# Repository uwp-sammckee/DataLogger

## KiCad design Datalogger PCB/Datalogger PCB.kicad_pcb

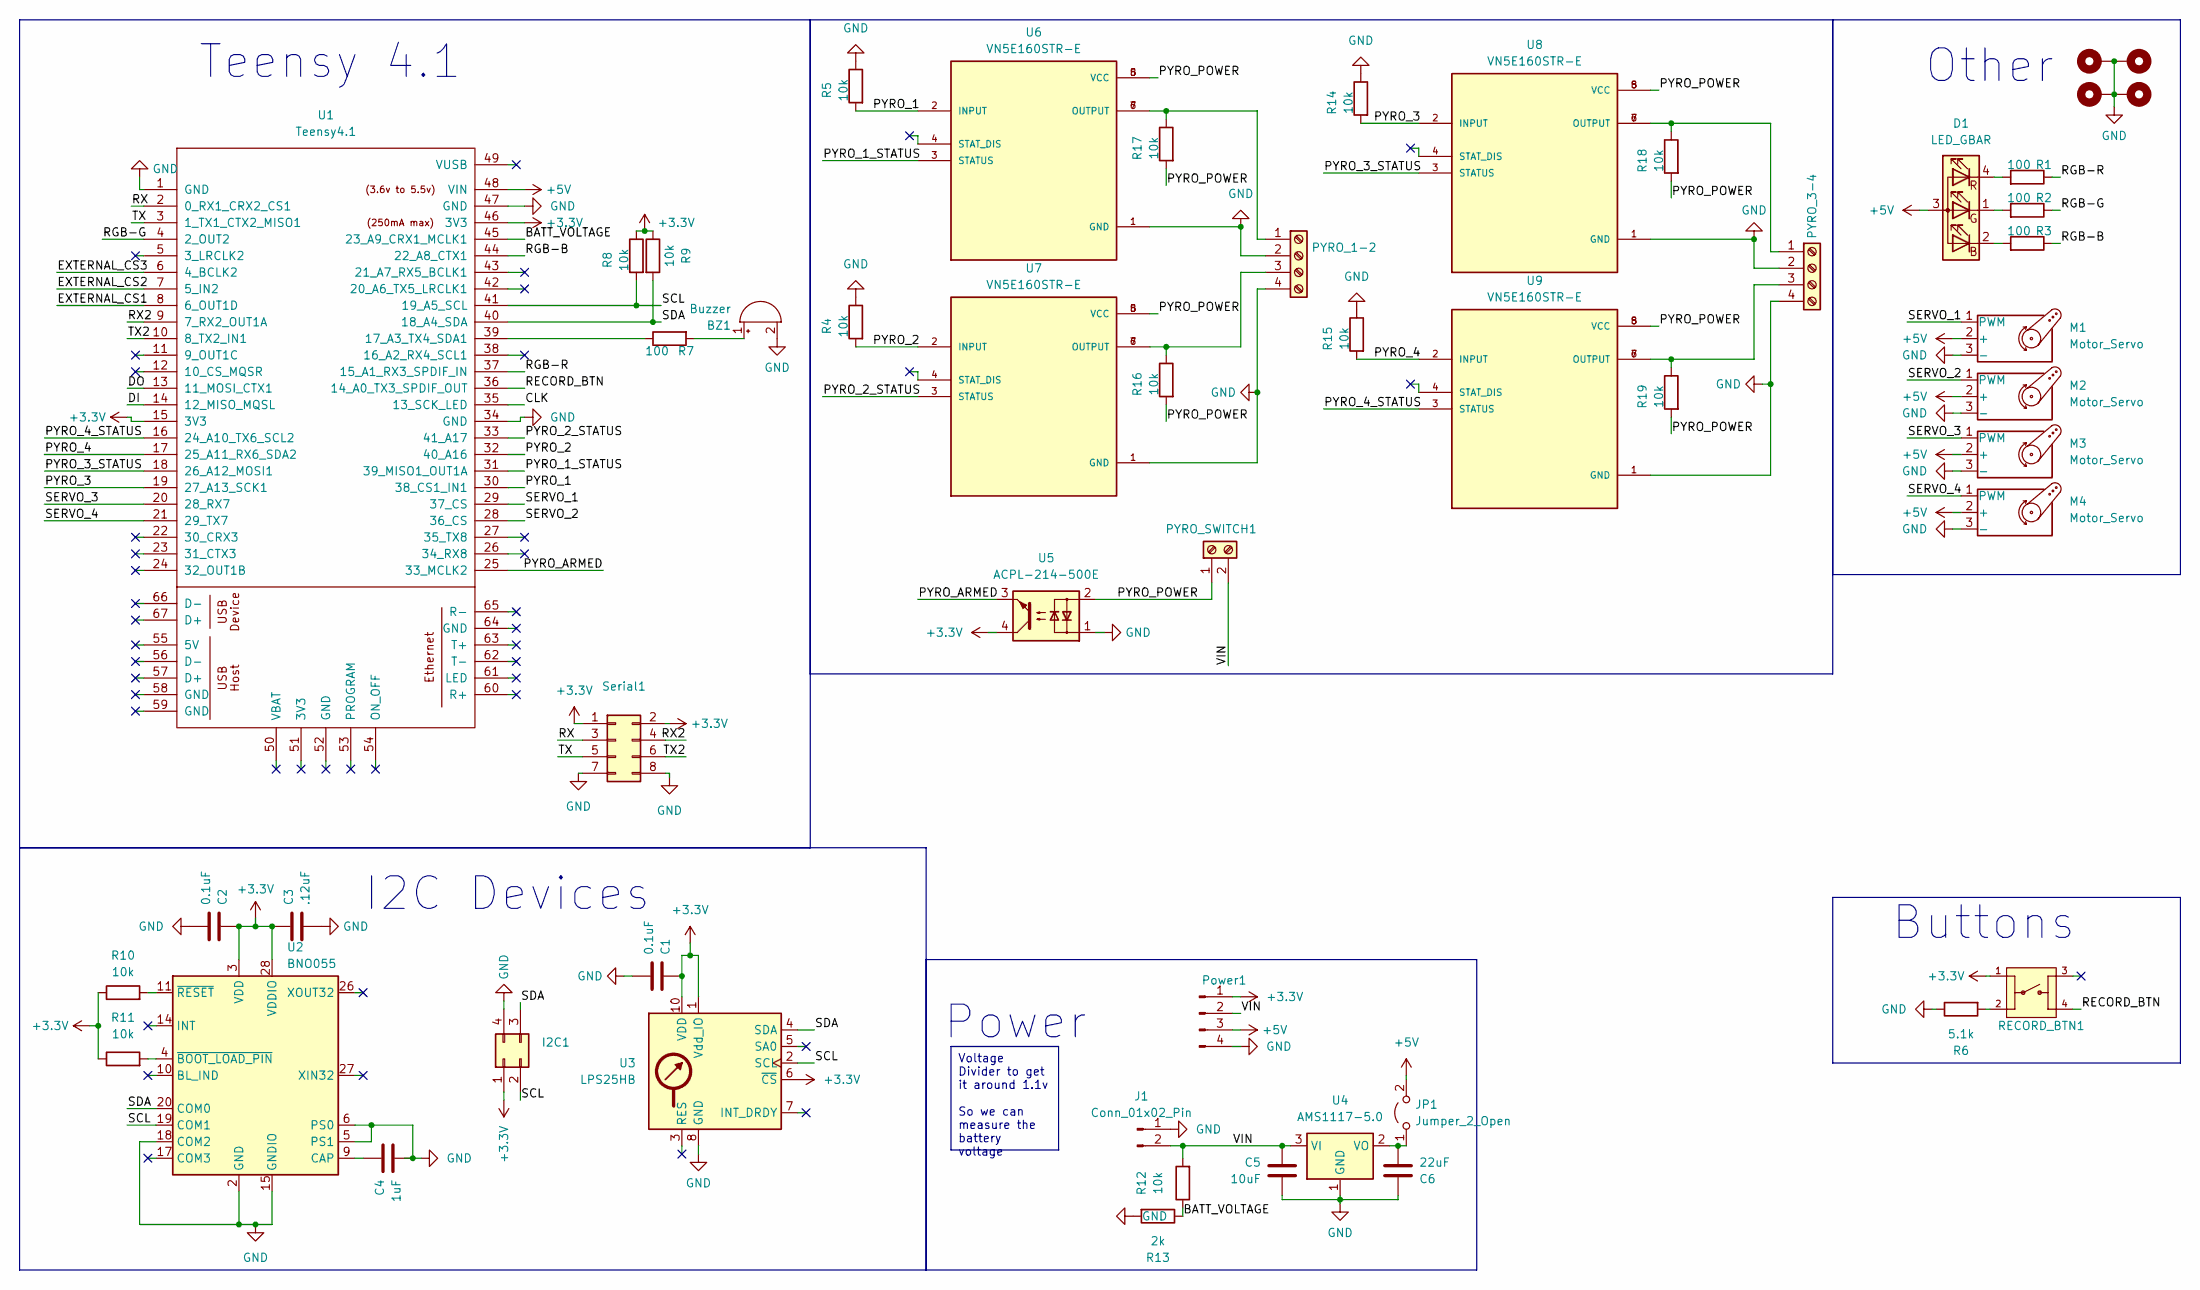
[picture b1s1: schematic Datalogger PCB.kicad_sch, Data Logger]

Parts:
BZ1: Buzzer; Buzzer_12x9.5RM7.6
C1, C2: 0.1uF; R_0603_1608Metric_Pad0.98x0.95mm_HandSolder
C3: .12uF; R_0603_1608Metric_Pad0.98x0.95mm_HandSolder
C4: 1uF; R_0603_1608Metric_Pad0.98x0.95mm_HandSolder
C5: 10uF; R_0603_1608Metric_Pad0.98x0.95mm_HandSolder
C6: 22uF; R_0603_1608Metric_Pad0.98x0.95mm_HandSolder
D1: LED_GBAR
H1, H2, H3, H4: MountingHole_Pad; MountingHole_3.2mm_M3_Pad_TopBottom
I2C1: Conn_02x02_Counter_Clockwise; PinHeader_2x02_P2.54mm_Vertical
J1: Conn_01x02_Pin; PinHeader_1x02_P2.54mm_Vertical
JP1: Jumper_2_Open; PinHeader_1x02_P2.54mm_Vertical
M1, M2, M3, M4: Motor_Servo; PinHeader_1x03_P2.54mm_Vertical
PYRO_1-2, PYRO_3-4: Screw_Terminal_01x04; TerminalBlock_bornier-4_P5.08mm
PYRO_SWITCH1: Screw_Terminal_01x02; TerminalBlock_bornier-2_P5.08mm
Power1: Conn_01x04_Pin; PinHeader_1x04_P2.54mm_Vertical
R1, R2, R3, R7: 100; R_0603_1608Metric_Pad0.98x0.95mm_HandSolder
R4, R5, R8, R9, R10, R11, R12, R14, R15, R16, R17, R18, R19: 10k; R_0603_1608Metric_Pad0.98x0.95mm_HandSolder
R6: 5.1k; R_0603_1608Metric_Pad0.98x0.95mm_HandSolder
R13: 2k; R_0603_1608Metric_Pad0.98x0.95mm_HandSolder
RECORD_BTN1: FSM8JH; SW_FSM8JH; PARTREV C10
Serial1: Conn_02x04_Odd_Even; PinHeader_2x04_P2.54mm_Vertical
U1: Teensy4.1; Teensy41
U2: BNO055; LGA-28_5.2x3.8mm_P0.5mm
U3: LPS25HB; ST_HLGA-10_2.5x2.5mm_P0.6mm_LayoutBorder3x2y
U4: AMS1117-5.0; SOT-223-3_TabPin2
U5: ACPL-214-500E; SOP-4_4.4x2.6mm_P1.27mm
U6, U7, U8, U9: VN5E160STR-E; SOIC127P600X175-8N; PARTREV 3

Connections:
+3.3V: C1.1, C2.1, C3.1, I2C1.1, Power1.1, R8.1, R9.1, R10.1, R11.1, RECORD_BTN1.1, Serial1.1, Serial1.2, U1.15 (3V3), U1.46 (3V3), U2.3 (VDD), U2.28 (VDDIO), U3.1 (Vdd_IO), U3.6 (~CS), U3.10 (VDD), U5.4
+5V: D1.3 (A), JP1.2 (B), M1.2 (+), M2.2 (+), M3.2 (+), M4.2 (+), Power1.3, U1.48 (VIN)
/BATT_VOLTAGE: R12.1, R13.1, U1.45 (23_A9_CRX1_MCLK1)
/CLK: U1.35 (13_SCK_LED)
/DI: U1.14 (12_MISO_MQSL)
/DO: U1.13 (11_MOSI_CTX1)
/EXTERNAL_CS1: U1.8 (6_OUT1D)
/EXTERNAL_CS2: U1.7 (5_IN2)
/EXTERNAL_CS3: U1.6 (4_BCLK2)
/PYRO_1: R5.2, U1.30 (38_CS1_IN1), U6.2 (INPUT)
/PYRO_1_STATUS: U1.31 (39_MISO1_OUT1A), U6.3 (STATUS)
/PYRO_2: R4.2, U1.32 (40_A16), U7.2 (INPUT)
/PYRO_2_STATUS: U1.33 (41_A17), U7.3 (STATUS)
/PYRO_3: R14.2, U1.19 (27_A13_SCK1), U8.2 (INPUT)
/PYRO_3_STATUS: U1.18 (26_A12_MOSI1), U8.3 (STATUS)
/PYRO_4: R15.2, U1.17 (25_A11_RX6_SDA2), U9.2 (INPUT)
/PYRO_4_STATUS: U1.16 (24_A10_TX6_SCL2), U9.3 (STATUS)
/PYRO_ARMED: U1.25 (33_MCLK2), U5.3
/PYRO_POWER: PYRO_SWITCH1.1, R16.2, R17.2, R18.2, R19.2, U5.2, U6.5 (VCC), U6.8 (VCC), U7.5 (VCC), U7.8 (VCC), U8.5 (VCC), U8.8 (VCC), U9.5 (VCC), U9.8 (VCC)
/RECORD_BTN: RECORD_BTN1.4, U1.36 (14_A0_TX3_SPDIF_OUT)
/RGB-B: R3.1, U1.44 (22_A8_CTX1)
/RGB-G: R2.1, U1.4 (2_OUT2)
/RGB-R: R1.1, U1.37 (15_A1_RX3_SPDIF_IN)
/RX: Serial1.3, U1.2 (0_RX1_CRX2_CS1)
/RX2: Serial1.4, U1.9 (7_RX2_OUT1A)
/SCL: I2C1.2, R8.2, U1.41 (19_A5_SCL), U2.19 (COM1), U3.2 (SCL)
/SDA: I2C1.3, R9.2, U1.40 (18_A4_SDA), U2.20 (COM0), U3.4 (SDA)
/SERVO_1: M1.1 (PWM), U1.29 (37_CS)
/SERVO_2: M2.1 (PWM), U1.28 (36_CS)
/SERVO_3: M3.1 (PWM), U1.20 (28_RX7)
/SERVO_4: M4.1 (PWM), U1.21 (29_TX7)
/TX: Serial1.5, U1.3 (1_TX1_CTX2_MISO1)
/TX2: Serial1.6, U1.10 (8_TX2_IN1)
/VIN: C5.1, J1.2, PYRO_SWITCH1.2, Power1.2, R12.2, U4.3 (VI)
GND: BZ1.2 (+), C1.2, C2.2, C3.2, C4.2, C5.2, C6.1, H1.1, H2.1, H3.1, H4.1, I2C1.4, J1.1, M1.3 (-), M2.3 (-), M3.3 (-), M4.3 (-), PYRO_1-2.2, PYRO_1-2.4, PYRO_3-4.2, PYRO_3-4.4, Power1.4, R4.1, R5.1, R6.1, R13.2, R14.1, R15.1, Serial1.7, Serial1.8, U1.1 (GND), U1.34 (GND), U1.47 (GND), U2.2 (GND), U2.5 (PS1), U2.6 (PS0), U2.15 (GNDIO), U2.16 (GNDIO), U2.18 (COM2), U2.25 (GNDIO), U3.8 (GND), U3.9 (GND), U4.1 (GND), U5.1, U6.1 (GND), U7.1 (GND), U8.1 (GND), U9.1 (GND)
unnamed: BZ1.1 (-), R7.2
unnamed: D1.2 (BK), R3.2
unnamed: D1.1 (GK), R2.2
unnamed: D1.4 (RK), R1.2
unnamed: C6.2, JP1.1 (A), U4.2 (VO)
unnamed: PYRO_1-2.1, R17.1, U6.6 (OUTPUT), U6.7 (OUTPUT)
unnamed: PYRO_1-2.3, R16.1, U7.6 (OUTPUT), U7.7 (OUTPUT)
unnamed: PYRO_3-4.1, R18.1, U8.6 (OUTPUT), U8.7 (OUTPUT)
unnamed: PYRO_3-4.3, R19.1, U9.6 (OUTPUT), U9.7 (OUTPUT)
unnamed: R6.2, RECORD_BTN1.2
unnamed: R7.1, U1.39 (17_A3_TX4_SDA1)
unnamed: C4.1, U2.9 (CAP)
unnamed: R11.2, U2.4 (~BOOT_LOAD_PIN)
unnamed: R10.2, U2.11 (~RESET)

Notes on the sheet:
Voltage Divider to get it around 1.1v So we can measure the battery voltage
Other
Teensy 4.1
Buttons
Power
I2C Devices

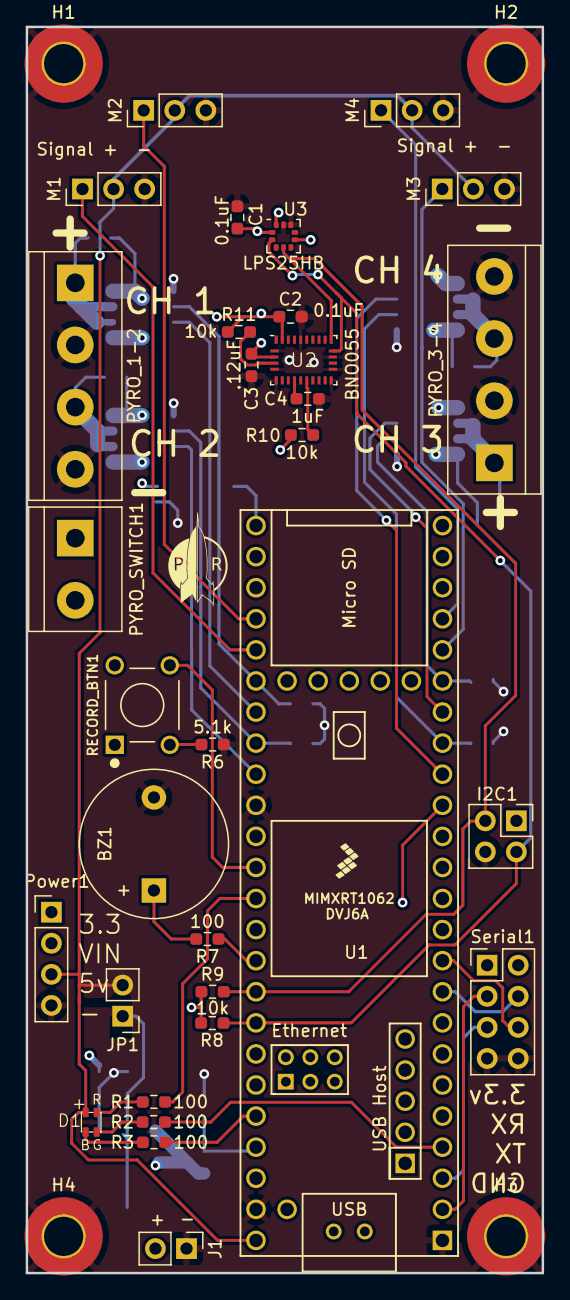
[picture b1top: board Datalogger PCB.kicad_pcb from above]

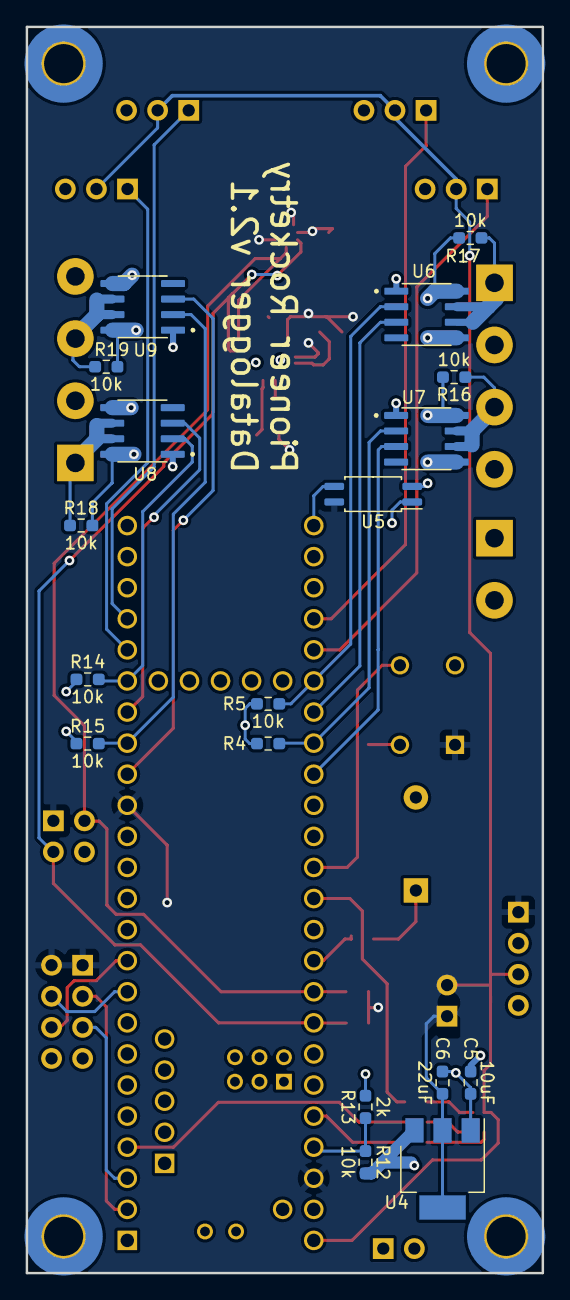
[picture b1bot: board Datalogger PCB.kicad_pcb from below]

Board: 4 copper layers, 42.2 x 101.8 mm, 53 parts (18 on the bottom side), 43 nets.

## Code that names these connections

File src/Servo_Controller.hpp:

// Servo_Controller.hpp
#ifndef SERVO_CONTROLLER_hpp
#define SERVO_CONTROLLER_hpp

#include <Arduino.h>
#include <Servo.h>

#define SERVO_1_PIN 37
#define SERVO_2_PIN 36
#define SERVO_3_PIN 28
#define SERVO_4_PIN 29

class Servo_Controller {
  private:
    static Servo servo1;
    static Servo servo2;
    static Servo servo3;
    static Servo servo4;

  public:
    static void begin() {
      servo1.attach(SERVO_1_PIN);
      servo2.attach(SERVO_2_PIN);
      servo3.attach(SERVO_3_PIN);
      servo4.attach(SERVO_4_PIN);
    }

    static void setServo1(int angle) {
      servo1.write(angle);
    }

    static void setServo2(int angle) {
      servo2.write(angle);
    }

    static void setServo3(int angle) {
      servo3.write(angle);
    }

    static void setServo4(int angle) {
      servo4.write(angle);
    }
};


#endif

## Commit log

2023-11-01 Code is able to do everything but it has a slow data log rate
2023-11-02 Fixed slow data logging
2023-11-02 Should of been pushed to Feature-1
2023-11-02 Revert "Should of been pushed to Feature-1"
    This reverts commit 4001e513602efce9f8fc61a58f293b3ddfdde305.
2023-11-02 Fixed data logging rate
2023-11-02 Revert back to first commit
2023-11-02 Converted Breadboard to Schematic
2023-11-03 Turn Schematic into PCB
2023-11-03 Made board smaller (about 1.6x4inch)
2023-11-06 Made Memory, ColorLED, and Buzzer classes to increase organization, and renamed the main Arduino file.
2023-11-12 Rename main file and add accelerometer class
2023-11-13 Added Barometer Class
2023-11-17 Added Test
2023-11-17 Added logo to PCB
2023-11-18 Reorganized code, could still be improve
2023-11-19 Reorganized for platformio
2023-11-19 Forget to ignore ./include
2023-11-19 forget to ignore vscode and include
2023-11-19 PCB-1 (#8)
    * Converted Breadboard to Schematic
    * Turn Schematic into PCB
    * Made board smaller (about 1.6x4inch)
    * Added Test
    * Added logo to PCB
    ---------
2023-11-19 release/1.0.0
2023-11-19 Added recording script
2023-12-02 Teensy 4.1 based datalogger with SMD parts
2023-12-03 Rev2 done?
2023-12-03 V2 of the PCB
2023-12-03 Coverted to 2 layer board
2023-12-03 Change some trace widths, as well as spread out traces, and fixed silk screen issues
2023-12-03 Added parts list
2023-12-04 Added screw terminal for switching on/off pyro channels
2023-12-04 Fixed Decoupling Cap for Barometer
2023-12-04 Added serial connector and power connectors
2023-12-05 Added check to see if all of the datapoints is NAN
2023-12-05 Added final check, and packetSize var
2023-12-06 Remove DUMP_BTN
2023-12-06 Final Revision
2023-12-06 Fix memory loop, and fix record.py, as well as defined baudrate inside of the platformio.ini file
2023-12-06 Fixed Const Loop Timing
2023-12-06 Added Sensor class, and made Barometer use it
2023-12-06 Moved the Baro/Acc into there respective folder
2023-12-06 Wrote version .1 of the BNO055 Lib
2023-12-07 Preliminary state machine code, will need to redo bounds for each state
2023-12-07 pull from main
2023-12-07 Rewrote update_sensor, and added very basic sensor fusion
2023-12-07 Created basuc LPS25HB library
2023-12-07 Redid the memory posistions, as well as replaced the sensors in the main file
2023-12-07 Removed Dump, And Erase Buttons
2023-12-07 Added very basic velocity calulations, and adjusted memory to make it work
2023-12-08 Added and validated states machine logic, not bounds
2023-12-08 moved README into base directory
2023-12-08 Added some naming conventions to coding conventions in README
2023-12-08 Corrected format of README
2023-12-09 Added Velocity
2023-12-09 funny commit
2023-12-09 Funny commit 2
2023-12-13 Redid BNO055 Lib, almost working
2023-12-14 test launch 1 code
2023-12-14 7 feature (#18)
    * Preliminary state machine code, will need to redo bounds for each state
    * pull from main
    * Added and validated states machine logic, not bounds
    * moved README into base directory
    * Added some naming conventions to coding conventions in README
    * Corrected format of README
2023-12-21 Made LED's connected to PWM pins
2023-12-21 Added pull down resistor to pyro channels
2023-12-26 Added datasheets
2023-12-26 Worked on the new libs
2024-01-04 Updated pin numbers for Buzzer, LED. Also have the first working version of the LPS25HB driver
2024-01-04 Removed extra print statements
2024-01-04 Updated basic LED, and buzzer drivers
2024-01-05 Added modified read to LPS25HB class
2024-01-05 Push buzzer, and LED into into in .hpp file, also made them static
2024-01-05 Removed BNO055 Submodule
2024-01-05 Finished BNO055 Lib
2024-01-05 Computed basic compass heading
2024-01-06 Removed MPU6050, and MPL3115A2 libs
2024-01-06 Data gets logged to flash chip
2024-01-06 Made the memory logging a bit faster
2024-01-06 Updated record.py as well as made other small mods
2024-01-06 small changes
2024-01-06 Added Solder Mask PDF
2024-01-06 Fixed a couple of pcb errors
2024-01-06 Added State Machine Logic UNTESTED
2024-01-06 Made var names fit the Naming Conventions
2024-01-06 Added SD Card Dump Support
2024-01-07 Added basic Pyro Channel Lib
2024-01-07 Added easly change able settings to BNO055
2024-01-07 Added path from descent to landed in case of a crash, also did some reformating
2024-01-08 Added error outputs for LED, and Buzzer, as well as Buzzer countdown when starting recording
2024-01-08 Changed small things
2024-01-09 Added parachute descent condition
2024-01-09 Added start_recording case to serial input
2024-01-10 Modified the 5v power rail a little
2024-01-10 Change baud rate to better fit 30hz
2024-01-18 Changed and flipped axis so Z is up, and X is out
2024-01-19 Added basic GPS driver as well as fixed typos in the Basic PYRO, as well has fixed tabing in LPS25HB.
2024-01-20 Updated and moved README
2024-01-27 Verifed GPS works
2024-01-28 Modified how data was printed, and logged so we can change precision
2024-01-28 Made packet_size in record.py change how many datapoints are searched for
2024-01-28 Made data class to add var names to make the code a little easier to read
2024-01-29 Recoded how long we can record for at 30hz and 60hz
2024-01-30 Added GPS command set to datasheets
2024-01-30 Made GPS run at 10hz
2024-01-31 Added basic servo wrapper
2024-02-01 not working code :(
2024-02-02 Implement Kalman filter for roll axis
2024-02-02 Changed FLASH_CS pin
2024-02-05 Modified Servo/Fin Controller, it now has offsets, and should have high resolution
2024-02-05 Added PitotTube code that might work will have to test
2024-02-07 roll and pitch were implemented
2024-02-11 Added basic control
2024-02-11 V2 pcb (#19)
    Completed PCB design
2024-02-12 Added kalman filter 100% written by chatgpt
2024-02-14 Stated working on altiude filtering
2024-02-15 Added Exponetial Moving Average to altitude
2024-02-18 Changed alt to relative alt (current-starting)
2024-02-18 Added Calibration offset saving/writing
2024-02-19 Arduino MadgwickAHRS
2024-02-19 Working Kalman Filter with ReefwingAHRS?
2024-02-19 Remove Derived data
2024-02-20 Did something
2024-02-21 Renamed offset to calibration, and add sensor offsets
2024-02-23 Made it run at 60hz, and updated fin controller sweep
2024-02-23 Basic 1 axis test that kind of works
2024-02-23 Switch to derivative based roll calc
2024-02-24 logging PID values now, also added back in code for servos 2-4
2024-02-24 Setup 2 fins for fin control
2024-02-25 Setup everything to be logged again
2024-02-25 Added serial radio
2024-03-01 Update Fin_Controller.hpp
    updated PID gain values
2024-03-01 Made connectors bigger and removed unused radio connector
2024-03-01 Logging everything now to radio
2024-03-03 Removed Diode and replaced with jumper
2024-03-03 Added pyro armed
2024-03-03 Added continuity resistors
2024-03-03 Grounded Connector
2024-03-03 Made power jumper standard
2024-03-08 Modified PCB
2024-03-14 Added pyro channel code, continuty testing doesn't work need to add resistor
